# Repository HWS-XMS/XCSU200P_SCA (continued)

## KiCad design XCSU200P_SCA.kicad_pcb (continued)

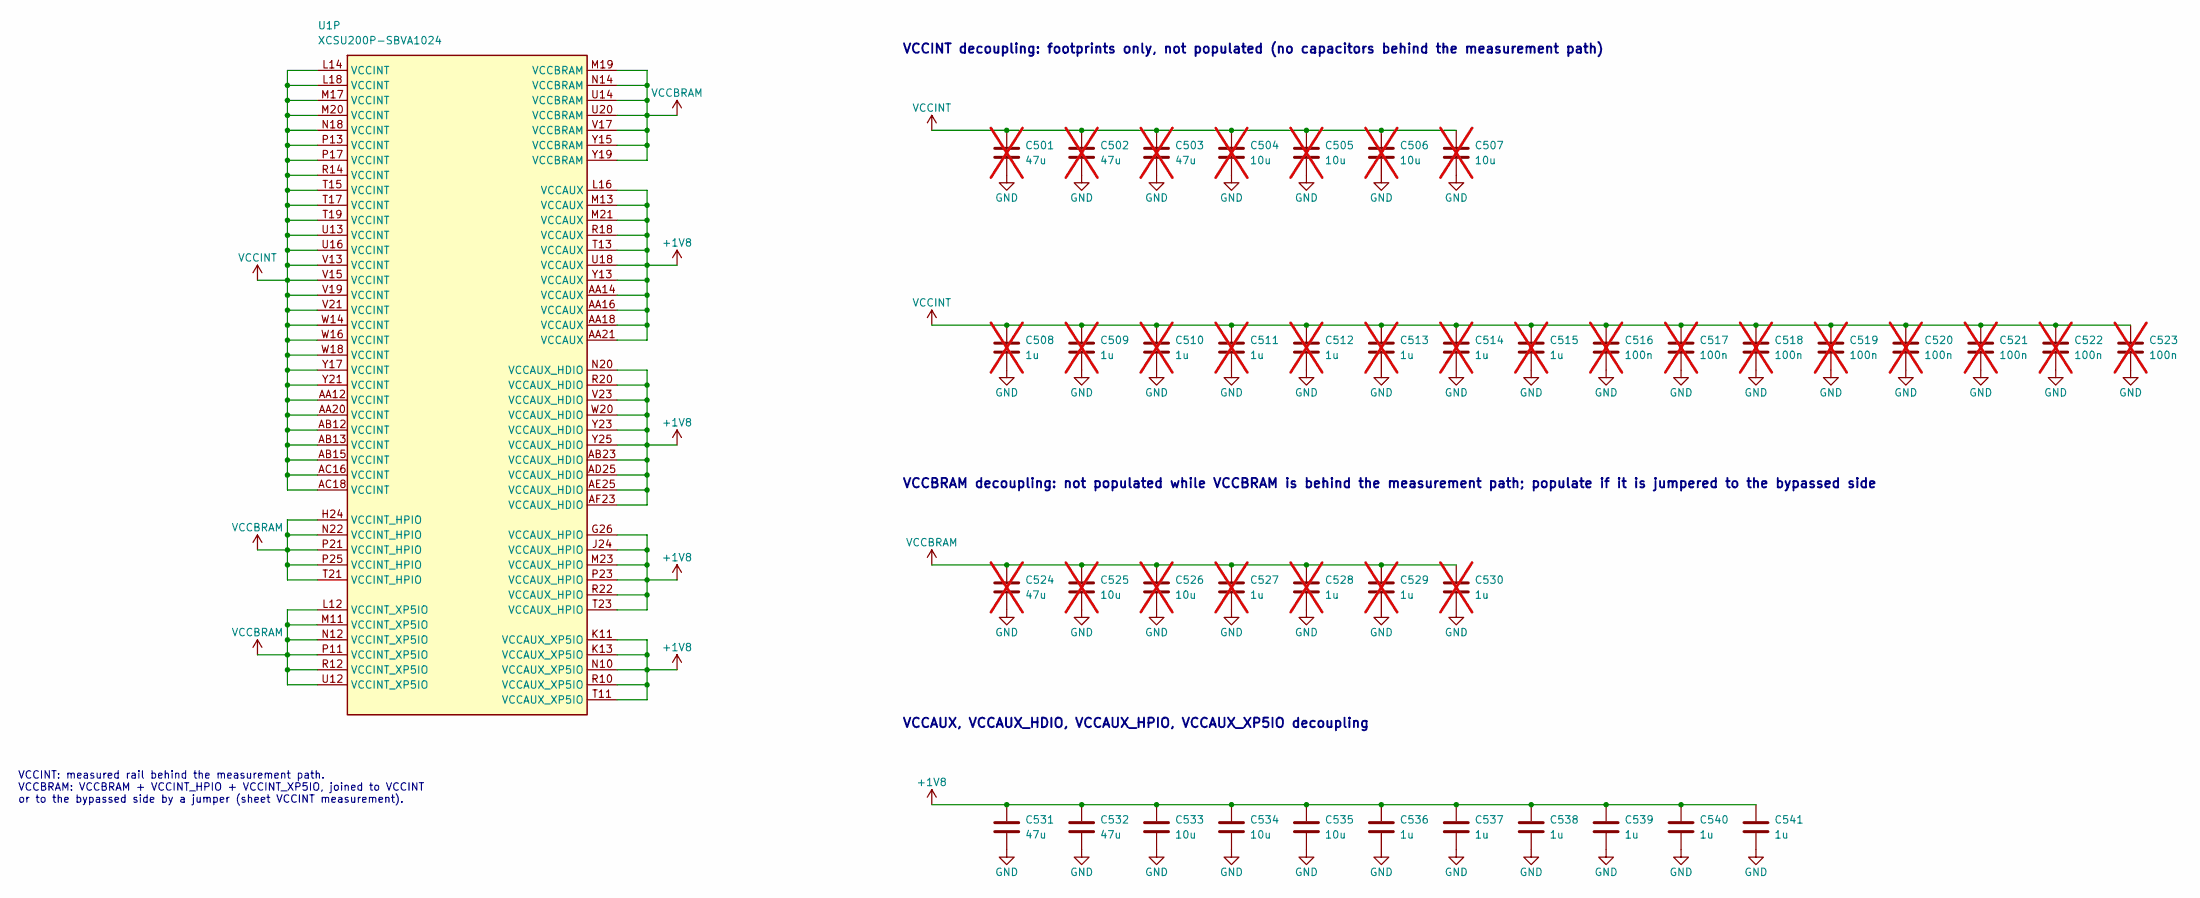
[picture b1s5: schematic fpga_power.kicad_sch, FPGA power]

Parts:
C501, C502, C503, C524: 47u; C_1206_3216Metric; MPN Samsung CL31A476MPHNNNE, 10 V X5R; LCSC C96123; not fitted
C504, C505, C506, C507, C525, C526: 10u; C_0603_1608Metric; MPN Samsung CL10A106KP8NNNC, 10 V X5R; LCSC C19702; not fitted
C508, C509, C510, C511, C512, C513, C514, C515, C527, C528, C529, C530: 1u; C_0402_1005Metric; MPN Samsung CL05A105KA5NQNC, 25 V X5R; LCSC C52923; not fitted
C516, C517, C518, C519, C520, C521, C522, C523: 100n; C_0402_1005Metric; MPN Samsung CL05B104KO5NNNC, 16 V X7R; LCSC C1525; not fitted
C531, C532: 47u; C_1206_3216Metric; MPN Samsung CL31A476MPHNNNE, 10 V X5R; LCSC C96123
C533, C534, C535: 10u; C_0603_1608Metric; MPN Samsung CL10A106KP8NNNC, 10 V X5R; LCSC C19702
C536, C537, C538, C539, C540, C541: 1u; C_0402_1005Metric; MPN Samsung CL05A105KA5NQNC, 25 V X5R; LCSC C52923
U1: XCSU200P-SBVA1024; AMD_SBVA1024_BGA-1024_27.0x27.0mm_Layout32x32_P0.8mm

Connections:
+1V8: C531.1, C532.1, C533.1, C534.1, C535.1, C536.1, C537.1, C538.1, C539.1, C540.1, C541.1, U1.AA14 (VCCAUX), U1.AA16 (VCCAUX), U1.AA18 (VCCAUX), U1.AA21 (VCCAUX), U1.AB23 (VCCAUX_HDIO), U1.AD25 (VCCAUX_HDIO), U1.AE25 (VCCAUX_HDIO), U1.AF23 (VCCAUX_HDIO), U1.G26 (VCCAUX_HPIO), U1.J24 (VCCAUX_HPIO), U1.K11 (VCCAUX_XP5IO), U1.K13 (VCCAUX_XP5IO), U1.L16 (VCCAUX), U1.M13 (VCCAUX), U1.M21 (VCCAUX), U1.M23 (VCCAUX_HPIO), U1.N10 (VCCAUX_XP5IO), U1.N20 (VCCAUX_HDIO), U1.P23 (VCCAUX_HPIO), U1.R10 (VCCAUX_XP5IO), U1.R18 (VCCAUX), U1.R20 (VCCAUX_HDIO), U1.R22 (VCCAUX_HPIO), U1.T11 (VCCAUX_XP5IO), U1.T13 (VCCAUX), U1.T23 (VCCAUX_HPIO), U1.U18 (VCCAUX), U1.V23 (VCCAUX_HDIO), U1.W20 (VCCAUX_HDIO), U1.Y13 (VCCAUX), U1.Y23 (VCCAUX_HDIO), U1.Y25 (VCCAUX_HDIO); also elsewhere on the board
GND: C501.2, C502.2, C503.2, C504.2, C505.2, C506.2, C507.2, C508.2, C509.2, C510.2, C511.2, C512.2, C513.2, C514.2, C515.2, C516.2, C517.2, C518.2, C519.2, C520.2, C521.2, C522.2, C523.2, C524.2, C525.2, C526.2, C527.2, C528.2, C529.2, C530.2, C531.2, C532.2, C533.2, C534.2, C535.2, C536.2, C537.2, C538.2, C539.2, C540.2, C541.2; also elsewhere on the board
VCCBRAM: C524.1, C525.1, C526.1, C527.1, C528.1, C529.1, C530.1, U1.H24 (VCCINT_HPIO), U1.L12 (VCCINT_XP5IO), U1.M11 (VCCINT_XP5IO), U1.M19 (VCCBRAM), U1.N12 (VCCINT_XP5IO), U1.N14 (VCCBRAM), U1.N22 (VCCINT_HPIO), U1.P11 (VCCINT_XP5IO), U1.P21 (VCCINT_HPIO), U1.P25 (VCCINT_HPIO), U1.R12 (VCCINT_XP5IO), U1.T21 (VCCINT_HPIO), U1.U12 (VCCINT_XP5IO), U1.U14 (VCCBRAM), U1.U20 (VCCBRAM), U1.V17 (VCCBRAM), U1.Y15 (VCCBRAM), U1.Y19 (VCCBRAM); also elsewhere on the board
VCCINT: C501.1, C502.1, C503.1, C504.1, C505.1, C506.1, C507.1, C508.1, C509.1, C510.1, C511.1, C512.1, C513.1, C514.1, C515.1, C516.1, C517.1, C518.1, C519.1, C520.1, C521.1, C522.1, C523.1, U1.AA12 (VCCINT), U1.AA20 (VCCINT), U1.AB12 (VCCINT), U1.AB13 (VCCINT), U1.AB15 (VCCINT), U1.AC16 (VCCINT), U1.AC18 (VCCINT), U1.L14 (VCCINT), U1.L18 (VCCINT), U1.M17 (VCCINT), U1.M20 (VCCINT), U1.N18 (VCCINT), U1.P13 (VCCINT), U1.P17 (VCCINT), U1.R14 (VCCINT), U1.T15 (VCCINT), U1.T17 (VCCINT), U1.T19 (VCCINT), U1.U13 (VCCINT), U1.U16 (VCCINT), U1.V13 (VCCINT), U1.V15 (VCCINT), U1.V19 (VCCINT), U1.V21 (VCCINT), U1.W14 (VCCINT), U1.W16 (VCCINT), U1.W18 (VCCINT), U1.Y17 (VCCINT), U1.Y21 (VCCINT); also elsewhere on the board

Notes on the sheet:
VCCINT: measured rail behind the measurement path. VCCBRAM: VCCBRAM + VCCINT_HPIO + VCCINT_XP5IO, joined to VCCINT or to the bypassed side by a jumper (sheet VCCINT measurement).
VCCINT decoupling: footprints only, not populated (no capacitors behind the measurement path)
VCCBRAM decoupling: not populated while VCCBRAM is behind the measurement path; populate if it is jumpered to the bypassed side
VCCAUX, VCCAUX_HDIO, VCCAUX_HPIO, VCCAUX_XP5IO decoupling

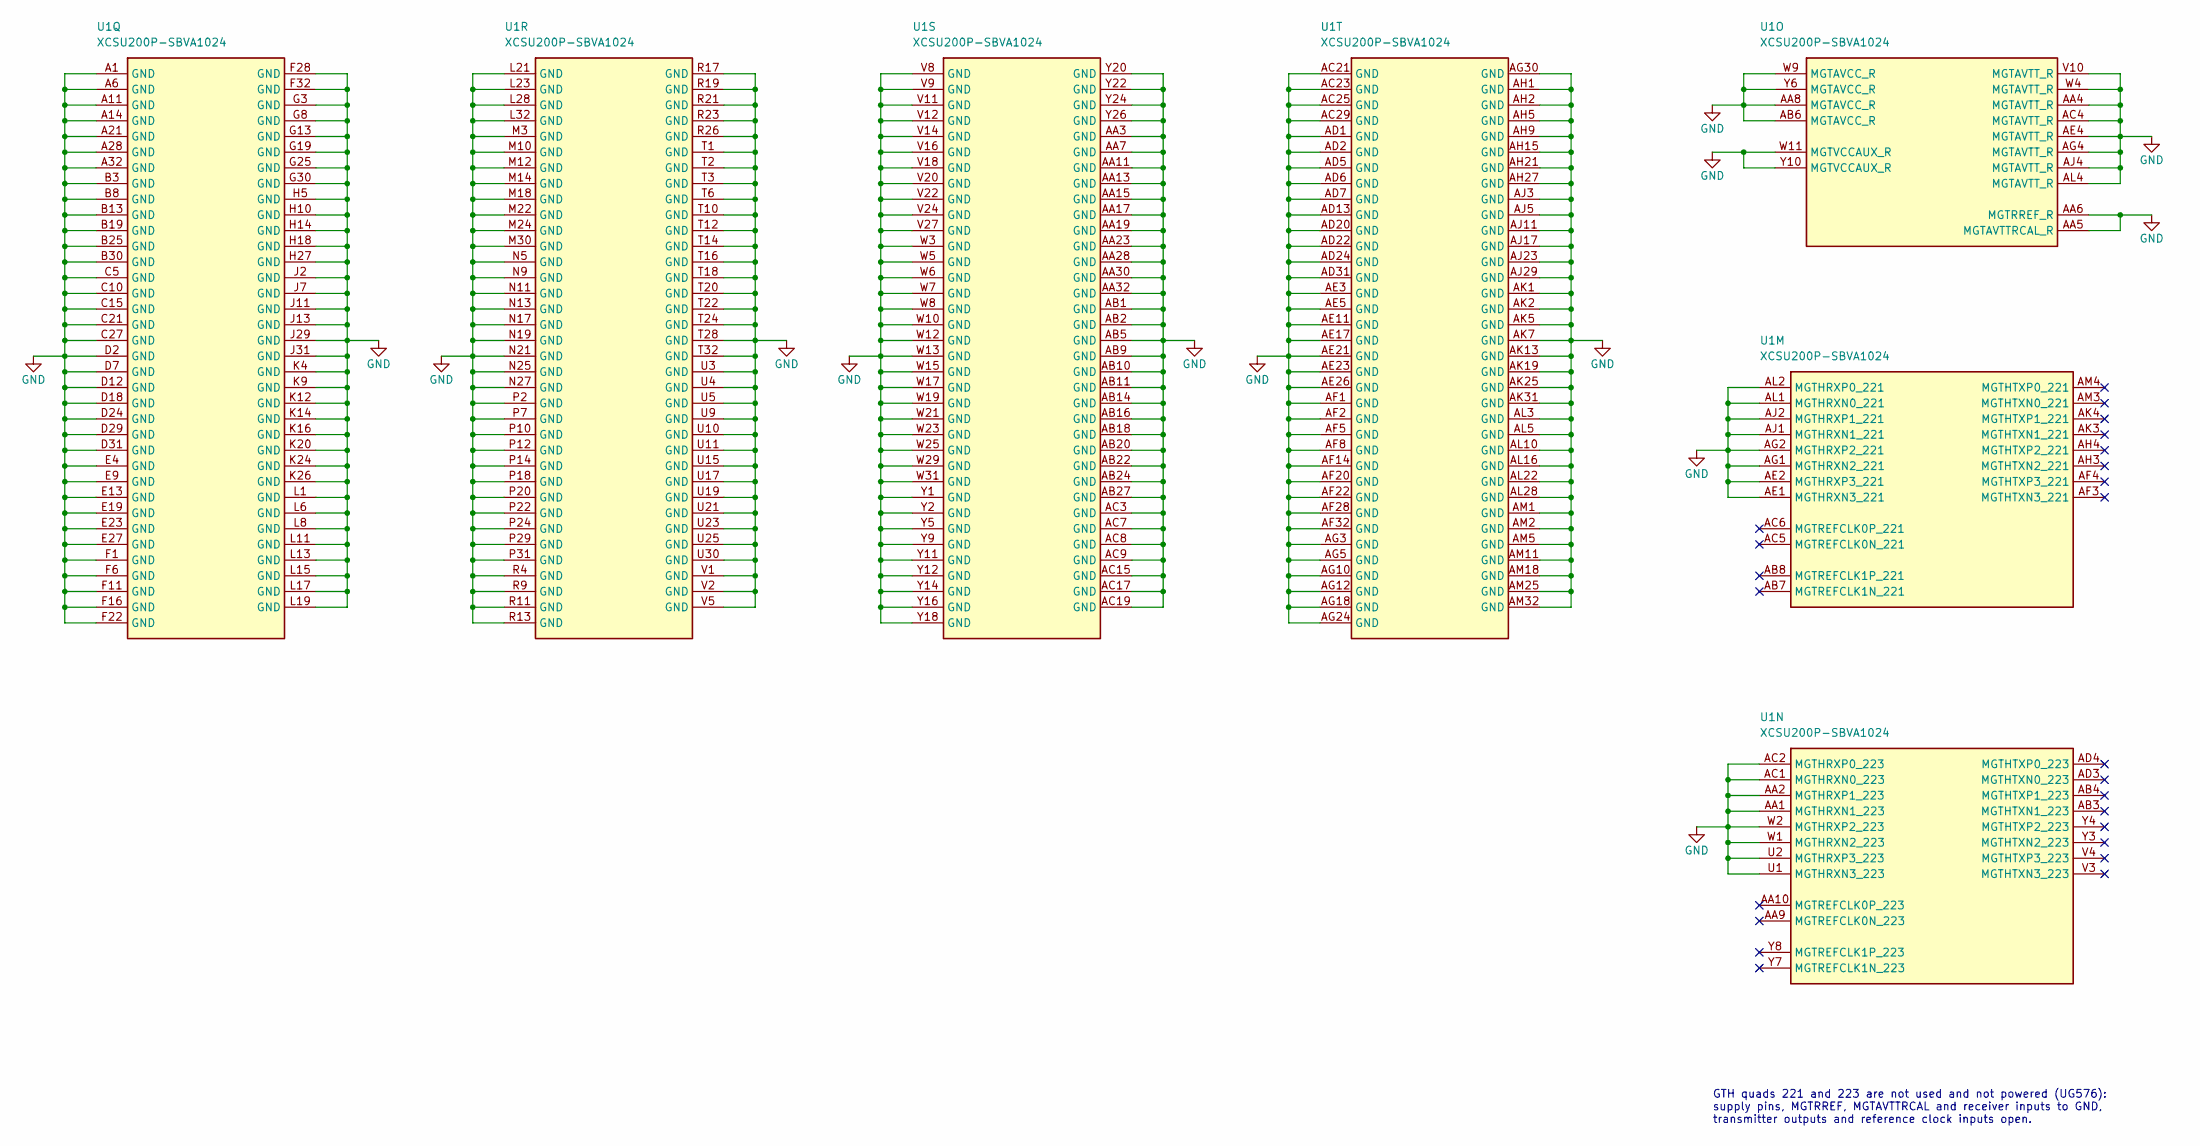
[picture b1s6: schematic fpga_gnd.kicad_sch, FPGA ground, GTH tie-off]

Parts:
U1: XCSU200P-SBVA1024; AMD_SBVA1024_BGA-1024_27.0x27.0mm_Layout32x32_P0.8mm

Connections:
GND: U1.A1 (GND), U1.A6 (GND), U1.A11 (GND), U1.A14 (GND), U1.A21 (GND), U1.A28 (GND), U1.A32 (GND), U1.AA1 (MGTHRXN1_223), U1.AA2 (MGTHRXP1_223), U1.AA3 (GND), U1.AA4 (MGTAVTT_R), U1.AA5 (MGTAVTTRCAL_R), U1.AA6 (MGTRREF_R), U1.AA7 (GND), U1.AA8 (MGTAVCC_R), U1.AA11 (GND), U1.AA13 (GND), U1.AA15 (GND), U1.AA17 (GND), U1.AA19 (GND), U1.AA23 (GND), U1.AA28 (GND), U1.AA30 (GND), U1.AA32 (GND), U1.AB1 (GND), U1.AB2 (GND), U1.AB5 (GND), U1.AB6 (MGTAVCC_R), U1.AB9 (GND), U1.AB10 (GND), U1.AB11 (GND), U1.AB14 (GND), U1.AB16 (GND), U1.AB18 (GND), U1.AB20 (GND), U1.AB22 (GND), U1.AB24 (GND), U1.AB27 (GND), U1.AC1 (MGTHRXN0_223), U1.AC2 (MGTHRXP0_223), U1.AC3 (GND), U1.AC4 (MGTAVTT_R), U1.AC7 (GND), U1.AC8 (GND), U1.AC9 (GND), U1.AC15 (GND), U1.AC17 (GND), U1.AC19 (GND), U1.AC21 (GND), U1.AC23 (GND), U1.AC25 (GND), U1.AC29 (GND), U1.AD1 (GND), U1.AD2 (GND), U1.AD5 (GND), U1.AD6 (GND), U1.AD7 (GND), U1.AD13 (GND), U1.AD20 (GND), U1.AD22 (GND), U1.AD24 (GND), U1.AD31 (GND), U1.AE1 (MGTHRXN3_221), U1.AE2 (MGTHRXP3_221), U1.AE3 (GND), U1.AE4 (MGTAVTT_R), U1.AE5 (GND), U1.AE11 (GND), U1.AE17 (GND), U1.AE21 (GND), U1.AE23 (GND), U1.AE26 (GND), U1.AF1 (GND), U1.AF2 (GND), U1.AF5 (GND), U1.AF8 (GND), U1.AF14 (GND), U1.AF20 (GND), U1.AF22 (GND), U1.AF28 (GND), U1.AF32 (GND), U1.AG1 (MGTHRXN2_221), U1.AG2 (MGTHRXP2_221), U1.AG3 (GND), U1.AG4 (MGTAVTT_R), U1.AG5 (GND), U1.AG10 (GND), U1.AG12 (GND), U1.AG18 (GND), U1.AG24 (GND), U1.AG30 (GND), U1.AH1 (GND), U1.AH2 (GND), U1.AH5 (GND), U1.AH9 (GND), U1.AH15 (GND), U1.AH21 (GND), U1.AH27 (GND), U1.AJ1 (MGTHRXN1_221), U1.AJ2 (MGTHRXP1_221), U1.AJ3 (GND), U1.AJ4 (MGTAVTT_R), U1.AJ5 (GND), U1.AJ11 (GND), U1.AJ17 (GND), U1.AJ23 (GND), U1.AJ29 (GND), U1.AK1 (GND), U1.AK2 (GND), U1.AK5 (GND), U1.AK7 (GND), U1.AK13 (GND), U1.AK19 (GND), U1.AK25 (GND), U1.AK31 (GND), U1.AL1 (MGTHRXN0_221), U1.AL2 (MGTHRXP0_221), U1.AL3 (GND), U1.AL4 (MGTAVTT_R), U1.AL5 (GND), U1.AL10 (GND), U1.AL16 (GND), U1.AL22 (GND), U1.AL28 (GND), U1.AM1 (GND), U1.AM2 (GND), U1.AM5 (GND), U1.AM11 (GND), U1.AM18 (GND), U1.AM25 (GND), U1.AM32 (GND), U1.B3 (GND), U1.B8 (GND), U1.B13 (GND), U1.B19 (GND), U1.B25 (GND), U1.B30 (GND), U1.C5 (GND), U1.C10 (GND), U1.C15 (GND), U1.C21 (GND), U1.C27 (GND), U1.D2 (GND), U1.D7 (GND), U1.D12 (GND), U1.D18 (GND), U1.D24 (GND), U1.D29 (GND), U1.D31 (GND), U1.E4 (GND), U1.E9 (GND), U1.E13 (GND), U1.E19 (GND), U1.E23 (GND), U1.E27 (GND), U1.F1 (GND), U1.F6 (GND), U1.F11 (GND), U1.F16 (GND), U1.F22 (GND), U1.F28 (GND), U1.F32 (GND), U1.G3 (GND), U1.G8 (GND), U1.G13 (GND), U1.G19 (GND), U1.G25 (GND), U1.G30 (GND), U1.H5 (GND), U1.H10 (GND), U1.H14 (GND), U1.H18 (GND), U1.H27 (GND), U1.J2 (GND), U1.J7 (GND), U1.J11 (GND), U1.J13 (GND), U1.J29 (GND), U1.J31 (GND), U1.K4 (GND), U1.K9 (GND), U1.K12 (GND), U1.K14 (GND), U1.K16 (GND), U1.K20 (GND), U1.K24 (GND), U1.K26 (GND), U1.L1 (GND), U1.L6 (GND), U1.L8 (GND), U1.L11 (GND), U1.L13 (GND), U1.L15 (GND), U1.L17 (GND), U1.L19 (GND), U1.L21 (GND), U1.L23 (GND), U1.L28 (GND), U1.L32 (GND), U1.M3 (GND), U1.M10 (GND), U1.M12 (GND), U1.M14 (GND), U1.M18 (GND), U1.M22 (GND), U1.M24 (GND), U1.M30 (GND), U1.N5 (GND), U1.N9 (GND), U1.N11 (GND), U1.N13 (GND), U1.N17 (GND), U1.N19 (GND), U1.N21 (GND), U1.N25 (GND), U1.N27 (GND), U1.P2 (GND), U1.P7 (GND), U1.P10 (GND), U1.P12 (GND), U1.P14 (GND), U1.P18 (GND), U1.P20 (GND), U1.P22 (GND), U1.P24 (GND), U1.P29 (GND), U1.P31 (GND), U1.R4 (GND), U1.R9 (GND), U1.R11 (GND), U1.R13 (GND), U1.R17 (GND), U1.R19 (GND), U1.R21 (GND), U1.R23 (GND), U1.R26 (GND), U1.T1 (GND), U1.T2 (GND), U1.T3 (GND), U1.T6 (GND), U1.T10 (GND), U1.T12 (GND), U1.T14 (GND), U1.T16 (GND), U1.T18 (GND), U1.T20 (GND), U1.T22 (GND), U1.T24 (GND), U1.T28 (GND), U1.T32 (GND), U1.U1 (MGTHRXN3_223), U1.U2 (MGTHRXP3_223), U1.U3 (GND), U1.U4 (GND), U1.U5 (GND), U1.U9 (GND), U1.U10 (GND), U1.U11 (GND), U1.U15 (GND), U1.U17 (GND), U1.U19 (GND), U1.U21 (GND), U1.U23 (GND), U1.U25 (GND), U1.U30 (GND), U1.V1 (GND), U1.V2 (GND), U1.V5 (GND), U1.V8 (GND), U1.V9 (GND), U1.V10 (MGTAVTT_R), U1.V11 (GND), U1.V12 (GND), U1.V14 (GND), U1.V16 (GND), U1.V18 (GND), U1.V20 (GND), U1.V22 (GND), U1.V24 (GND), U1.V27 (GND), U1.W1 (MGTHRXN2_223), U1.W2 (MGTHRXP2_223), U1.W3 (GND), U1.W4 (MGTAVTT_R), U1.W5 (GND), U1.W6 (GND), U1.W7 (GND), U1.W8 (GND), U1.W9 (MGTAVCC_R), U1.W10 (GND), U1.W11 (MGTVCCAUX_R), U1.W12 (GND), U1.W13 (GND), U1.W15 (GND), U1.W17 (GND), U1.W19 (GND), U1.W21 (GND), U1.W23 (GND), U1.W25 (GND), U1.W29 (GND), U1.W31 (GND), U1.Y1 (GND), U1.Y2 (GND), U1.Y5 (GND), U1.Y6 (MGTAVCC_R), U1.Y9 (GND), U1.Y10 (MGTVCCAUX_R), U1.Y11 (GND), U1.Y12 (GND), U1.Y14 (GND), U1.Y16 (GND), U1.Y18 (GND), U1.Y20 (GND), U1.Y22 (GND), U1.Y24 (GND), U1.Y26 (GND); also elsewhere on the board

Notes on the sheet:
GTH quads 221 and 223 are not used and not powered (UG576): supply pins, MGTRREF, MGTAVTTRCAL and receiver inputs to GND, transmitter outputs and reference clock inputs open.

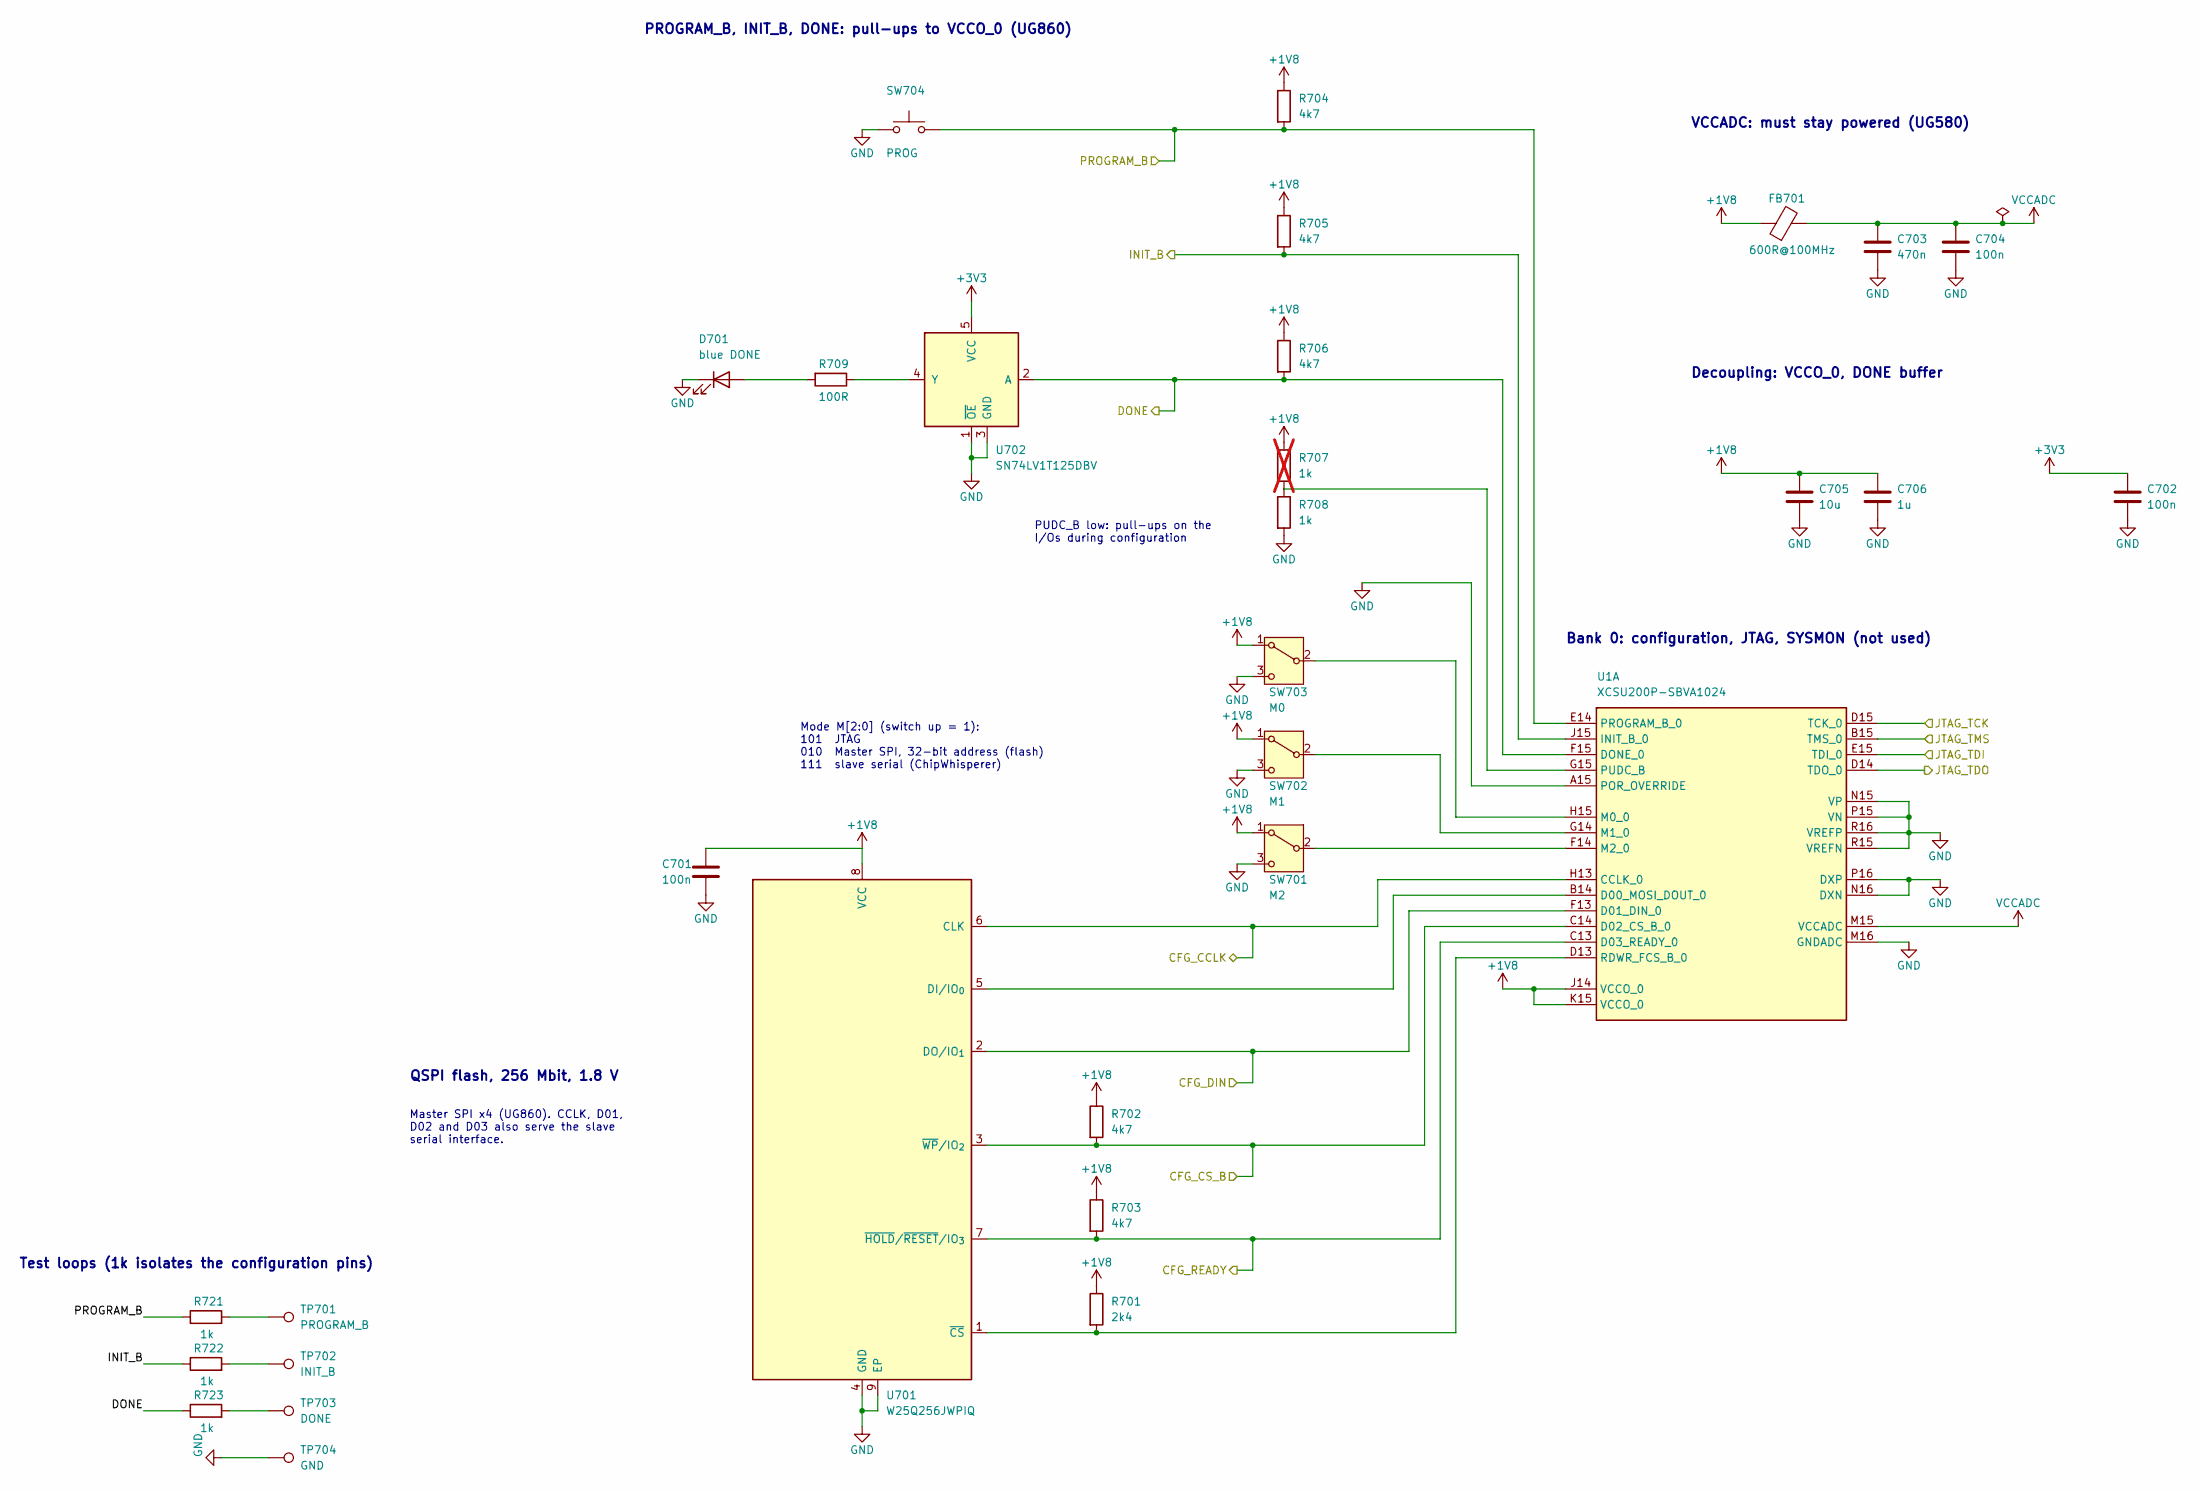
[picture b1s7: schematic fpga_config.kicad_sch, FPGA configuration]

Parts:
C701, C702, C704: 100n; C_0402_1005Metric; MPN Samsung CL05B104KO5NNNC, 16 V X7R; LCSC C1525
C703: 470n; C_0402_1005Metric; MPN Samsung CL05A474KP5NNNC, 10 V X5R; LCSC C47339
C705: 10u; C_0603_1608Metric; MPN Samsung CL10A106KP8NNNC, 10 V X5R; LCSC C19702
C706: 1u; C_0402_1005Metric; MPN Samsung CL05A105KA5NQNC, 25 V X5R; LCSC C52923
D701: blue DONE; LED_0603_1608Metric; MPN Hubei KENTO KT-0603B, 3.1 V; LCSC C2288
FB701: 600R@100MHz; L_0603_1608Metric; MPN Sunlord GZ1608D601TF, 200 mA; LCSC C1002
R701: 2k4; R_0402_1005Metric; MPN UNI-ROYAL 0402WGF2401TCE; LCSC C25882
R702, R703, R704, R705, R706: 4k7; R_0402_1005Metric; MPN UNI-ROYAL 0402WGF4701TCE; LCSC C25900
R707: 1k; R_0402_1005Metric; MPN UNI-ROYAL 0402WGF1001TCE; LCSC C11702; not fitted
R708, R721, R722, R723: 1k; R_0402_1005Metric; MPN UNI-ROYAL 0402WGF1001TCE; LCSC C11702
R709: 100R; R_0402_1005Metric; MPN UNI-ROYAL 0402WGF1000TCE; LCSC C25076
SW701: M2; SW_SPDT_Shouhan_MSK12C02; LCSC C431540
SW702: M1; SW_SPDT_Shouhan_MSK12C02; LCSC C431540
SW703: M0; SW_SPDT_Shouhan_MSK12C02; LCSC C431540
SW704: PROG; SW_Push_1P1T_XKB_TS-1187A; MPN XKB TS-1187A-B-A-B; LCSC C318884
TP701: PROGRAM_B; TestPoint_Keystone_5005-5009_Compact_NoCircle; MPN Keystone 5007 (white); LCSC C238125
TP702: INIT_B; TestPoint_Keystone_5005-5009_Compact_NoCircle; MPN Keystone 5007 (white); LCSC C238125
TP703: DONE; TestPoint_Keystone_5005-5009_Compact_NoCircle; MPN Keystone 5007 (white); LCSC C238125
TP704: GND; TestPoint_Keystone_5005-5009_Compact_NoCircle; MPN Keystone 5006 (black); LCSC C2906764
U1: XCSU200P-SBVA1024; AMD_SBVA1024_BGA-1024_27.0x27.0mm_Layout32x32_P0.8mm
U701: W25Q256JWPIQ; WSON-8-1EP_6x5mm_P1.27mm_EP3.4x4.3mm; LCSC C5362614
U702: SN74LV1T125DBV; SOT-23-5; MPN TI SN74LV1T125DBVR; LCSC C473338

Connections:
+1V8: C701.1, C705.1, C706.1, FB701.1, R701.1, R702.1, R703.1, R704.1, R705.1, R706.1, R707.1, SW701.1 (A), SW702.1 (A), SW703.1 (A), U1.J14 (VCCO_0), U1.K15 (VCCO_0), U701.8 (VCC); also elsewhere on the board
+3V3: C702.1, U702.5 (VCC); also elsewhere on the board
/ChipWhisperer/CFG_CCLK: U1.H13 (CCLK_0), U701.6 (CLK); also elsewhere on the board
/ChipWhisperer/CFG_CS_B: R702.2, U1.C14 (D02_CS_B_0), U701.3 (~WP/IO_{2}); also elsewhere on the board
/ChipWhisperer/CFG_DIN: U1.F13 (D01_DIN_0), U701.2 (DO/IO_{1}); also elsewhere on the board
/ChipWhisperer/CFG_READY: R703.2, U1.C13 (D03_READY_0), U701.7 (~HOLD/~RESET/IO_{3}); also elsewhere on the board
/FPGA configuration/DONE: R706.2, R723.1, U1.F15 (DONE_0), U702.2 (A); also elsewhere on the board
/FPGA configuration/INIT_B: R705.2, R722.1, U1.J15 (INIT_B_0); also elsewhere on the board
/FPGA configuration/PROGRAM_B: R704.2, R721.1, SW704.1, U1.E14 (PROGRAM_B_0); also elsewhere on the board
/JTAG_TCK: U1.D15 (TCK_0); also elsewhere on the board
/JTAG_TDI: U1.E15 (TDI_0); also elsewhere on the board
/JTAG_TDO: U1.D14 (TDO_0); also elsewhere on the board
/JTAG_TMS: U1.B15 (TMS_0); also elsewhere on the board
GND: C701.2, C702.2, C703.2, C704.2, C705.2, C706.2, D701.1 (K), R708.2, SW701.3 (C), SW702.3 (C), SW703.3 (C), SW704.2, TP704.1 (1_1), U1.A15 (POR_OVERRIDE), U1.M16 (GNDADC), U1.N15 (VP), U1.N16 (DXN), U1.P15 (VN), U1.P16 (DXP), U1.R15 (VREFN), U1.R16 (VREFP), U701.4 (GND), U701.9 (EP), U702.1 (~OE), U702.3 (GND); also elsewhere on the board
unnamed: D701.2 (A), R709.2
unnamed: R721.2, TP701.1 (1_1)
unnamed: R722.2, TP702.1 (1_1)
unnamed: R723.2, TP703.1 (1_1)
unnamed: SW701.2 (B), U1.F14 (M2_0)
unnamed: SW702.2 (B), U1.G14 (M1_0)
unnamed: SW703.2 (B), U1.H15 (M0_0)
unnamed: U1.B14 (D00_MOSI_DOUT_0), U701.5 (DI/IO_{0})
unnamed: R707.2, R708.1, U1.G15 (PUDC_B)
unnamed: R701.2, U1.D13 (RDWR_FCS_B_0), U701.1 (~CS)
unnamed: R709.1, U702.4 (Y)
VCCADC: C703.1, C704.1, FB701.2, U1.M15 (VCCADC)

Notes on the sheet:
Bank 0: configuration, JTAG, SYSMON (not used)
PROGRAM_B, INIT_B, DONE: pull-ups to VCCO_0 (UG860)
PUDC_B low: pull-ups on the I/Os during configuration
Mode M[2:0] (switch up = 1): 101 JTAG 010 Master SPI, 32-bit address (flash) 111 slave serial (ChipWhisperer)
QSPI flash, 256 Mbit, 1.8 V
Master SPI x4 (UG860). CCLK, D01, D02 and D03 also serve the slave serial interface.
Test loops (1k isolates the configuration pins)
VCCADC: must stay powered (UG580)
Decoupling: VCCO_0, DONE buffer

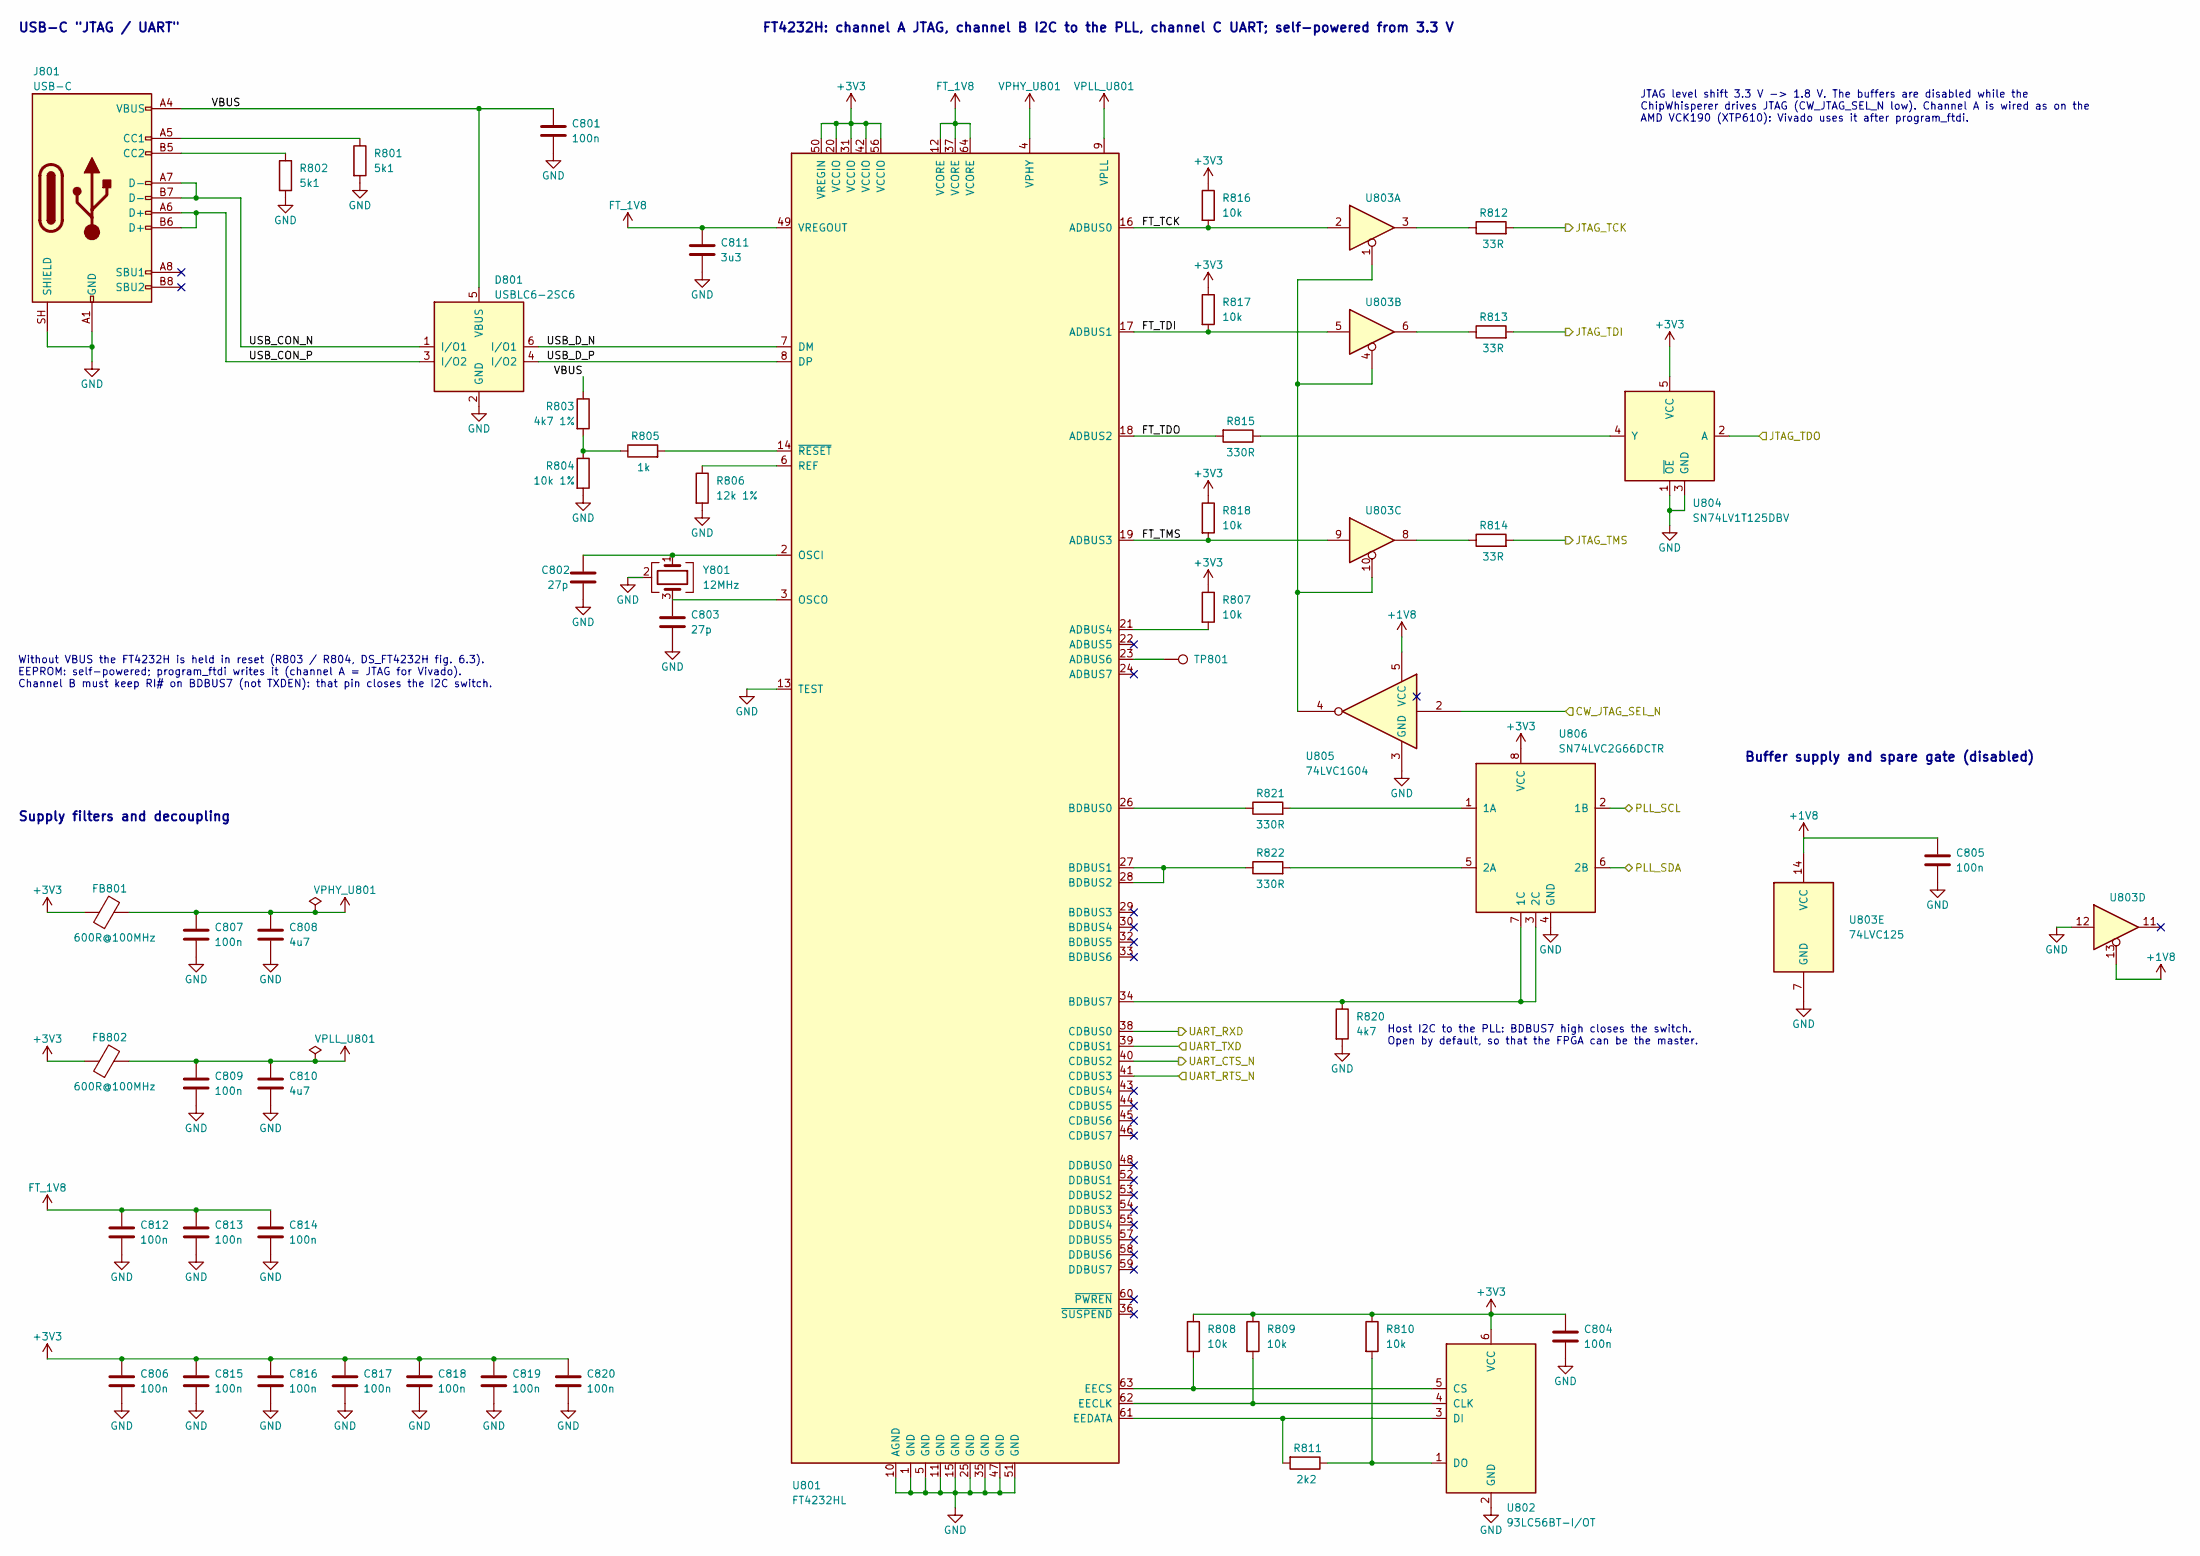
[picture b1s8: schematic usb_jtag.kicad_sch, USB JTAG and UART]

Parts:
C801, C804, C805, C806, C807, C809, C812, C813, C814, C815, C816, C817, C818, C819, C820: 100n; C_0402_1005Metric; MPN Samsung CL05B104KO5NNNC, 16 V X7R; LCSC C1525
C802, C803: 27p; C_0402_1005Metric; MPN FH 0402CG270J500NT, 50 V C0G; LCSC C1557
C808, C810: 4u7; C_0603_1608Metric; MPN Samsung CL10A475KO8NNNC, 16 V X5R; LCSC C19666
C811: 3u3; C_0603_1608Metric; MPN Samsung CL10A335KP8NNNC, 10 V X5R; LCSC C51412
D801: USBLC6-2SC6; SOT-23-6; LCSC C7519
FB801, FB802: 600R@100MHz; L_0603_1608Metric; MPN Sunlord GZ1608D601TF, 200 mA; LCSC C1002
J801: USB-C; USB_C_Receptacle_HRO_TYPE-C-31-M-12_Edge; LCSC C165948
R801, R802: 5k1; R_0402_1005Metric; MPN UNI-ROYAL 0402WGF5101TCE; LCSC C25905
R803: 4k7 1%; R_0402_1005Metric; MPN UNI-ROYAL 0402WGF4701TCE; LCSC C25900
R804: 10k 1%; R_0402_1005Metric; MPN UNI-ROYAL 0402WGF1002TCE; LCSC C25744
R805: 1k; R_0402_1005Metric; MPN UNI-ROYAL 0402WGF1001TCE; LCSC C11702
R806: 12k 1%; R_0402_1005Metric; MPN UNI-ROYAL 0402WGF1202TCE; LCSC C25752
R807, R808, R809, R810, R816, R817, R818: 10k; R_0402_1005Metric; MPN UNI-ROYAL 0402WGF1002TCE; LCSC C25744
R811: 2k2; R_0402_1005Metric; MPN UNI-ROYAL 0402WGF2201TCE; LCSC C25879
R812, R813, R814: 33R; R_0402_1005Metric; MPN UNI-ROYAL 0402WGF330JTCE; LCSC C25105
R815, R821, R822: 330R; R_0402_1005Metric; MPN UNI-ROYAL 0402WGF3300TCE; LCSC C25104
R820: 4k7; R_0402_1005Metric; MPN UNI-ROYAL 0402WGF4701TCE; LCSC C25900
TP801: AD6; TestPoint_Pad_D1.0mm
U801: FT4232HL; LQFP-64_10x10mm_P0.5mm; LCSC C56742
U802: 93LC56BT-I/OT; SOT-23-6; LCSC C190271
U803: 74LVC125; TSSOP-14_4.4x5mm_P0.65mm; MPN TI SN74LVC125APWR; LCSC C7813
U804: SN74LV1T125DBV; SOT-23-5; LCSC C473338
U805: 74LVC1G04; SOT-23-5; LCSC C7827
U806: SN74LVC2G66DCTR; SSOP-8_2.95x2.8mm_P0.65mm; MPN TI SN74LVC2G66DCTR; LCSC C2651913
Y801: 12MHz; Crystal_SMD_3225-4Pin_3.2x2.5mm; LCSC C9002

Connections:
+1V8: C805.1, U803.13, U803.14 (VCC), U805.5 (VCC); also elsewhere on the board
+3V3: C804.1, C806.1, C815.1, C816.1, C817.1, C818.1, C819.1, C820.1, FB801.1, FB802.1, R807.1, R808.1, R809.1, R810.1, R816.1, R817.1, R818.1, U801.20 (VCCIO), U801.31 (VCCIO), U801.42 (VCCIO), U801.50 (VREGIN), U801.56 (VCCIO), U802.6 (VCC), U804.5 (VCC), U806.8 (VCC); also elsewhere on the board
/CW_JTAG_SEL_N: U805.2; also elsewhere on the board
/FPGA banks 3.3 V/UART_CTS_N: U801.40 (CDBUS2); also elsewhere on the board
/FPGA banks 3.3 V/UART_RTS_N: U801.41 (CDBUS3); also elsewhere on the board
/FPGA banks 3.3 V/UART_RXD: U801.38 (CDBUS0); also elsewhere on the board
/FPGA banks 3.3 V/UART_TXD: U801.39 (CDBUS1); also elsewhere on the board
/JTAG_TCK: R812.2; also elsewhere on the board
/JTAG_TDI: R813.2; also elsewhere on the board
/JTAG_TDO: U804.2 (A); also elsewhere on the board
/JTAG_TMS: R814.2; also elsewhere on the board
/PLL_SCL: U806.2 (1B); also elsewhere on the board
/PLL_SDA: U806.6 (2B); also elsewhere on the board
/USB JTAG and UART/FT_TCK: R816.2, U801.16 (ADBUS0), U803.2
/USB JTAG and UART/FT_TDI: R817.2, U801.17 (ADBUS1), U803.5
/USB JTAG and UART/FT_TDO: R815.2, U801.18 (ADBUS2)
/USB JTAG and UART/FT_TMS: R818.2, U801.19 (ADBUS3), U803.9
/USB JTAG and UART/USB_CON_N: D801.1 (I/O1), J801.A7 (D-), J801.B7 (D-)
/USB JTAG and UART/USB_CON_P: D801.3 (I/O2), J801.A6 (D+), J801.B6 (D+)
/USB JTAG and UART/USB_D_N: D801.6 (I/O1), U801.7 (DM)
/USB JTAG and UART/USB_D_P: D801.4 (I/O2), U801.8 (DP)
/USB JTAG and UART/VBUS: C801.1, D801.5 (VBUS), J801.A4 (VBUS), J801.A9 (VBUS), J801.B4 (VBUS), J801.B9 (VBUS), R803.1
FT_1V8: C811.1, C812.1, C813.1, C814.1, U801.12 (VCORE), U801.37 (VCORE), U801.49 (VREGOUT), U801.64 (VCORE)
GND: C801.2, C802.2, C803.2, C804.2, C805.2, C806.2, C807.2, C808.2, C809.2, C810.2, C811.2, C812.2, C813.2, C814.2, C815.2, C816.2, C817.2, C818.2, C819.2, C820.2, D801.2 (GND), J801.A1 (GND), J801.A12 (GND), J801.B1 (GND), J801.B12 (GND), J801.SH (SHIELD), R801.2, R802.2, R804.2, R806.2, R820.2, U801.1 (GND), U801.5 (GND), U801.10 (AGND), U801.11 (GND), U801.13 (TEST), U801.15 (GND), U801.25 (GND), U801.35 (GND), U801.47 (GND), U801.51 (GND), U802.2 (GND), U803.7 (GND), U803.12, U804.1 (~OE), U804.3 (GND), U805.3 (GND), U806.4 (GND), Y801.2 (G), Y801.4 (G); also elsewhere on the board
unnamed: J801.A5 (CC1), R801.1
unnamed: J801.B5 (CC2), R802.1
unnamed: R803.2, R804.1, R805.1
unnamed: R812.1, U803.3
unnamed: R813.1, U803.6
unnamed: R814.1, U803.8
unnamed: R807.2, U801.21 (ADBUS4)
unnamed: TP801.1 (1_1), U801.23 (ADBUS6)
unnamed: R821.1, U801.26 (BDBUS0)
unnamed: R822.1, U801.27 (BDBUS1), U801.28 (BDBUS2)
unnamed: R820.1, U801.34 (BDBUS7), U806.3 (2C), U806.7 (1C)
unnamed: R809.2, U801.62 (EECLK), U802.4 (CLK)
unnamed: R808.2, U801.63 (EECS), U802.5 (CS)
unnamed: R811.2, U801.61 (EEDATA), U802.3 (DI)
unnamed: C802.1, U801.2 (OSCI), Y801.1
unnamed: C803.1, U801.3 (OSCO), Y801.3
unnamed: R806.1, U801.6 (REF)
unnamed: R805.2, U801.14 (~RESET)
unnamed: R810.2, R811.1, U802.1 (DO)
unnamed: U803.1, U803.4, U803.10, U805.4
unnamed: R815.1, U804.4 (Y)
unnamed: R821.2, U806.1 (1A)
unnamed: R822.2, U806.5 (2A)
VPHY_U801: C807.1, C808.1, FB801.2, U801.4 (VPHY)
VPLL_U801: C809.1, C810.1, FB802.2, U801.9 (VPLL)

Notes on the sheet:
USB-C "JTAG / UART"
FT4232H: channel A JTAG, channel B I2C to the PLL, channel C UART; self-powered from 3.3 V
Host I2C to the PLL: BDBUS7 high closes the switch. Open by default, so that the FPGA can be the master.
JTAG level shift 3.3 V -> 1.8 V. The buffers are disabled while the ChipWhisperer drives JTAG (CW_JTAG_SEL_N low). Channel A is wired as on the AMD VCK190 (XTP610): Vivado uses it after program_ftdi.
Buffer supply and spare gate (disabled)
Without VBUS the FT4232H is held in reset (R803 / R804, DS_FT4232H fig. 6.3). EEPROM: self-powered; program_ftdi writes it (channel A = JTAG for Vivado). Channel B must keep RI# on BDBUS7 (not TXDEN): that pin closes the I2C switch.
Supply filters and decoupling

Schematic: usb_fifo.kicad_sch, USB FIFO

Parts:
C901, C905, C906, C907, C908, C909, C912, C913, C914, C915, C916: 100n; C_0402_1005Metric; MPN Samsung CL05B104KO5NNNC, 16 V X7R; LCSC C1525
C902: 10n; C_0402_1005Metric; MPN Samsung CL05B103KB5NNNC, 50 V X7R; LCSC C15195
C903, C904: 27p; C_0402_1005Metric; MPN FH 0402CG270J500NT, 50 V C0G; LCSC C1557
C910, C911: 4u7; C_0603_1608Metric; MPN Samsung CL10A475KO8NNNC, 16 V X5R; LCSC C19666
D901: USBLC6-2SC6; SOT-23-6; LCSC C7519
FB901, FB902: 600R@100MHz; L_0603_1608Metric; MPN Sunlord GZ1608D601TF, 200 mA; LCSC C1002
J901: USB-C; USB_C_Receptacle_HRO_TYPE-C-31-M-12_Edge; LCSC C165948
R901, R902: 5k1; R_0402_1005Metric; MPN UNI-ROYAL 0402WGF5101TCE; LCSC C25905
R903: 27R; R_0402_1005Metric; MPN UNI-ROYAL 0402WGF270JTCE; LCSC C25100
R904: 39k; R_0402_1005Metric; MPN UNI-ROYAL 0402WGF3902TCE; LCSC C25783
R905, R907, R908, R909: 10k; R_0402_1005Metric; MPN UNI-ROYAL 0402WGF1002TCE; LCSC C25744
R906: 12k 1%; R_0402_1005Metric; MPN UNI-ROYAL 0402WGF1202TCE; LCSC C25752
R910: 2k2; R_0402_1005Metric; MPN UNI-ROYAL 0402WGF2201TCE; LCSC C25879
U901: FT232HL; LQFP-48_7x7mm_P0.5mm; LCSC C51997
U902: 93LC56BT-I/OT; SOT-23-6; LCSC C190271
Y901: 12MHz; Crystal_SMD_3225-4Pin_3.2x2.5mm; LCSC C9002

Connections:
+3V3: C905.1, C910.1, C911.1, C912.1, C913.1, C914.1, C915.1, C916.1, FB901.1, FB902.1, R905.1, R907.1, R908.1, R909.1, U901.12 (VCCIO), U901.24 (VCCIO), U901.39 (VCCD), U901.40 (VREGIN), U901.46 (VCCIO), U902.6 (VCC); also elsewhere on the board
/FPGA banks 3.3 V/FIFO_AC8: U901.32 (ACBUS8); also elsewhere on the board
/FPGA banks 3.3 V/FIFO_AC9: U901.33 (ACBUS9); also elsewhere on the board
/FPGA banks 3.3 V/FIFO_CLK: R903.2; also elsewhere on the board
/FPGA banks 3.3 V/FIFO_D0: U901.13 (ADBUS0); also elsewhere on the board
/FPGA banks 3.3 V/FIFO_D1: U901.14 (ADBUS1); also elsewhere on the board
/FPGA banks 3.3 V/FIFO_D2: U901.15 (ADBUS2); also elsewhere on the board
/FPGA banks 3.3 V/FIFO_D3: U901.16 (ADBUS3); also elsewhere on the board
/FPGA banks 3.3 V/FIFO_D4: U901.17 (ADBUS4); also elsewhere on the board
/FPGA banks 3.3 V/FIFO_D5: U901.18 (ADBUS5); also elsewhere on the board
/FPGA banks 3.3 V/FIFO_D6: U901.19 (ADBUS6); also elsewhere on the board
/FPGA banks 3.3 V/FIFO_D7: U901.20 (ADBUS7); also elsewhere on the board
/FPGA banks 3.3 V/FIFO_OE_N: U901.30 (ACBUS6); also elsewhere on the board
/FPGA banks 3.3 V/FIFO_RD_N: U901.26 (ACBUS2); also elsewhere on the board
/FPGA banks 3.3 V/FIFO_RXF_N: U901.21 (ACBUS0); also elsewhere on the board
/FPGA banks 3.3 V/FIFO_SIWU_N: U901.28 (ACBUS4); also elsewhere on the board
/FPGA banks 3.3 V/FIFO_TXE_N: U901.25 (ACBUS1); also elsewhere on the board
/FPGA banks 3.3 V/FIFO_WR_N: U901.27 (ACBUS3); also elsewhere on the board
/USB FIFO/USB_CON_N: D901.1 (I/O1), J901.A7 (D-), J901.B7 (D-)
/USB FIFO/USB_CON_P: D901.3 (I/O2), J901.A6 (D+), J901.B6 (D+)
/USB FIFO/USB_D_N: D901.6 (I/O1), U901.6 (DM)
/USB FIFO/USB_D_P: D901.4 (I/O2), U901.7 (DP)
/USB FIFO/VBUS: C901.1, D901.5 (VBUS), J901.A4 (VBUS), J901.A9 (VBUS), J901.B4 (VBUS), J901.B9 (VBUS), R904.1
GND: C901.2, C902.2, C903.2, C904.2, C905.2, C906.2, C907.2, C908.2, C909.2, C910.2, C911.2, C912.2, C913.2, C914.2, C915.2, C916.2, D901.2 (GND), J901.A1 (GND), J901.A12 (GND), J901.B1 (GND), J901.B12 (GND), J901.SH (SHIELD), R901.2, R902.2, R906.2, U901.4 (AGND), U901.9 (AGND), U901.10 (GND), U901.11 (GND), U901.22 (GND), U901.23 (GND), U901.35 (GND), U901.36 (GND), U901.41 (AGND), U901.42 (TEST), U901.47 (GND), U901.48 (GND), U902.2 (GND), Y901.2 (G), Y901.4 (G); also elsewhere on the board
unnamed: J901.A5 (CC1), R901.1
unnamed: J901.B5 (CC2), R902.1
unnamed: R903.1, U901.29 (ACBUS5)
unnamed: R904.2, U901.31 (ACBUS7)
unnamed: R908.2, U901.44 (EECLK), U902.4 (CLK)
unnamed: R907.2, U901.45 (EECS), U902.5 (CS)
unnamed: R910.2, U901.43 (EEDATA), U902.3 (DI)
unnamed: R906.1, U901.5 (REF)
unnamed: C909.1, U901.37 (VCCA)
unnamed: C908.1, U901.38 (VCCCORE)
unnamed: C903.1, U901.1 (XCSI), Y901.1
unnamed: C904.1, U901.2 (XCSO), Y901.3
unnamed: C902.1, R905.2, U901.34 (~RESET)
unnamed: R909.2, R910.1, U902.1 (DO)
VPHY_U901: C906.1, FB901.2, U901.3 (VPHY)
VPLL_U901: C907.1, FB902.2, U901.8 (VPLL)

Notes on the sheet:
USB-C "DATA"
FT232H, synchronous 245 FIFO, self-powered from 3.3 V
60 MHz
VBUS sense: set "Suspend on ACBus7 low" in the EEPROM
Supply filters and decoupling
